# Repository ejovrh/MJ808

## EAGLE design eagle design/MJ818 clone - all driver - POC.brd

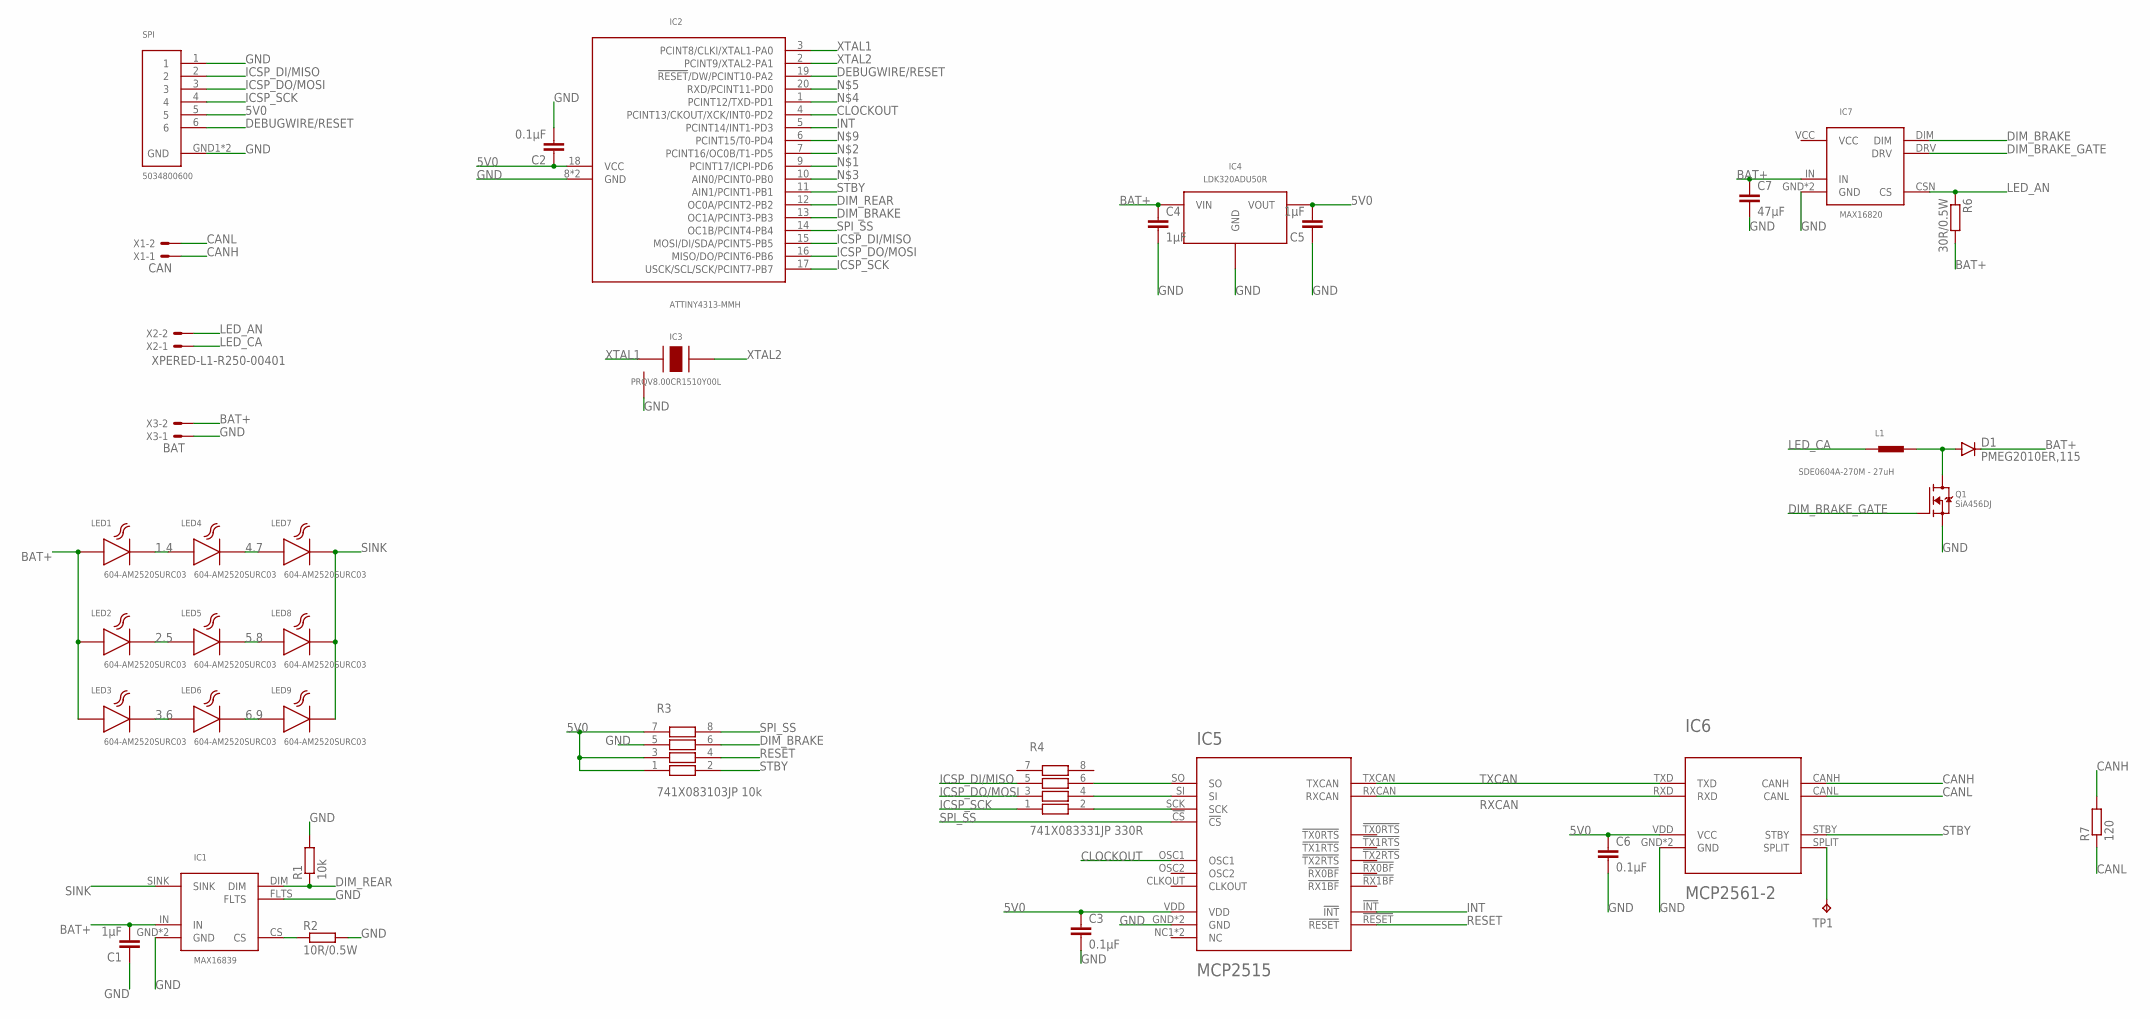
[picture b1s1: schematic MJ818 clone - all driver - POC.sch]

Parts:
C1, C4, C5: 1μF; C0402
C2, C3, C6: 0.1μF; C0402
C7: 47μF; C0805
D1: PMEG2010ER,115; SOD123
IC1: MAX16839; TDFN-6-EP
IC2: ATTINY4313-MMH; VQFN-20
IC3: PRQV8.00CR1510Y00L; SMT
IC4: LDK320ADU50R; SOT-89-D
IC5: MCP2515; QFN20
IC6: MCP2561-2; DFN10
IC7: MAX16820; TDFN-6-EP
L1: SDE0604A-270M - 27uH; SMT
LED1, LED2, LED3, LED4, LED5, LED6, LED7, LED8, LED9: 604-AM2520SURC03; SMD
Q1: SiA456DJ; SC-70-6
R1: 10k; R0402
R2: 10R/0.5W; R0603
R3: 741X083103JP 10k; 0402
R4: 741X083331JP 330R; 0402
R6: 30R/0.5W; R1206
R7: 120; R0805
SPI: 5034800600; SMT
TP1: TPB2,54; B2,54
X1: CAN; 22-23-2021
X2: XPERED-L1-R250-00401; 22-23-2021
X3: BAT; 22-23-2021

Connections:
1.4: LED1.C, LED4.A
2.5: LED2.C, LED5.A
3.6: LED3.C, LED6.A
4.7: LED4.C, LED7.A
5.8: LED5.C, LED8.A
5V0: C2.1, C3.1, C5.2, C6.1, IC2.18 (VCC), IC4.VOUT, IC5.VDD, IC6.VDD (VCC), R3.1, R3.3, R3.7, SPI.5
6.9: LED6.C, LED9.A
BAT+: C1.2, C4.1, C7.1, D1.C, IC1.IN, IC4.VIN, IC7.IN, LED1.A, LED2.A, LED3.A, R6.2, X3.2
CANH: IC6.CANH, R7.2, X1.1
CANL: IC6.CANL, R7.1, X1.2
CLOCKOUT: IC2.4 (PCINT13/CKOUT/XCK/INT0-PD2), IC5.OSC1
CS: IC1.CS, R2.1
DEBUGWIRE/RESET: IC2.19 (!RESET!/DW/PCINT10-PA2), SPI.6
DIM_BRAKE: IC2.13 (OC1A/PCINT3-PB3), IC7.DIM, R3.6
DIM_BRAKE_DRAIN: D1.A, L1.P$2, Q1.D
DIM_BRAKE_GATE: IC7.DRV, Q1.G
DIM_REAR: IC1.DIM, IC2.12 (OC0A/PCINT2-PB2), R1.1
GND: C1.1, C2.2, C3.2, C4.2, C5.1, C6.2, C7.2, IC1.FLTS, IC1.GND, IC1.GND1 (GND), IC2.8 (GND), IC2.GND, IC3.GND, IC4.GND, IC5.GND, IC5.GND6 (GND), IC6.GND, IC6.VSS (GND), IC7.GND, IC7.GND1 (GND), Q1.S, R1.2, R2.2, R3.5, SPI.1, SPI.GND1 (GND), SPI.GND2 (GND), X3.1
ICSP_DI/MISO: IC2.15 (MOSI/DI/SDA/PCINT5-PB5), R4.5, SPI.2
ICSP_DO/MOSI: IC2.16 (MISO/DO/PCINT6-PB6), R4.3, SPI.3
ICSP_SCK: IC2.17 (USCK/SCL/SCK/PCINT7-PB7), R4.1, SPI.4
INT: IC2.5 (PCINT14/INT1-PD3), IC5.!INT!
LED_AN: IC7.CSN (CS), R6.1, X2.2
LED_CA: L1.P$1, X2.1
RESET: IC5.!RESET!, R3.4
RXCAN: IC5.RXCAN, IC6.RXD
SINK: IC1.SINK, LED7.C, LED8.C, LED9.C
SPI_MISO: IC5.SO, R4.6
SPI_MOSI: IC5.SI, R4.4
SPI_SCK: IC5.SCK, R4.2
SPI_SS: IC2.14 (OC1B/PCINT4-PB4), IC5.!CS!, R3.8
SPLIT: IC6.SPLIT, TP1.TP
STBY: IC2.11 (AIN1/PCINT1-PB1), IC6.STBY, R3.2
TXCAN: IC5.TXCAN, IC6.TXD
VCC: IC7.VCC
XTAL1: IC2.3 (PCINT8/CLKI/XTAL1-PA0), IC3.XTAL1
XTAL2: IC2.2 (PCINT9/XTAL2-PA1), IC3.XTAL2

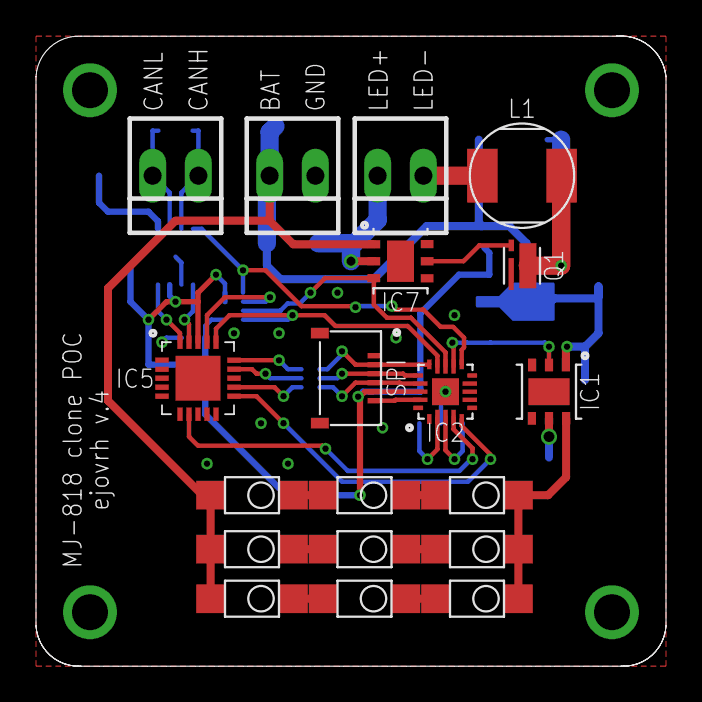
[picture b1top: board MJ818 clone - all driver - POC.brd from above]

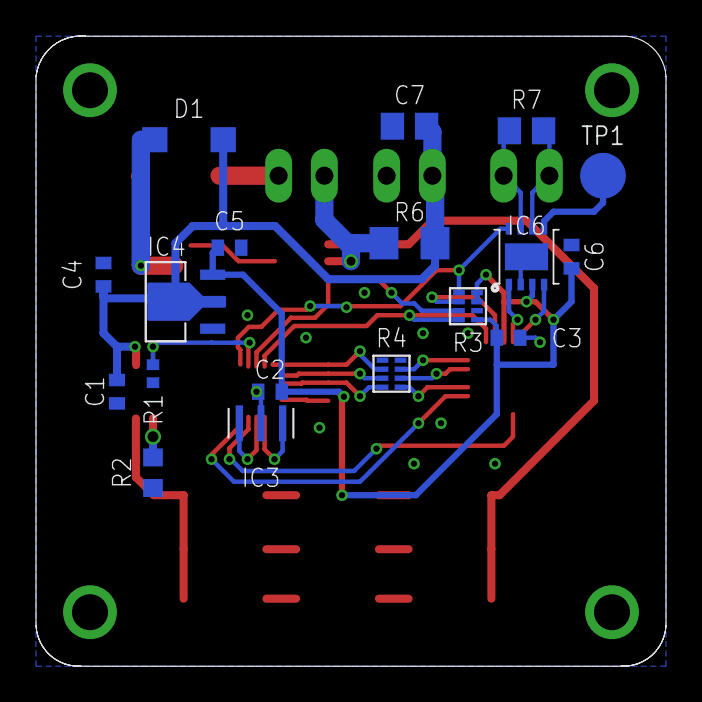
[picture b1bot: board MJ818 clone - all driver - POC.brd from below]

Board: 2 copper layers, 35.0 x 35.0 mm, 37 parts (18 on the bottom side), 36 nets.

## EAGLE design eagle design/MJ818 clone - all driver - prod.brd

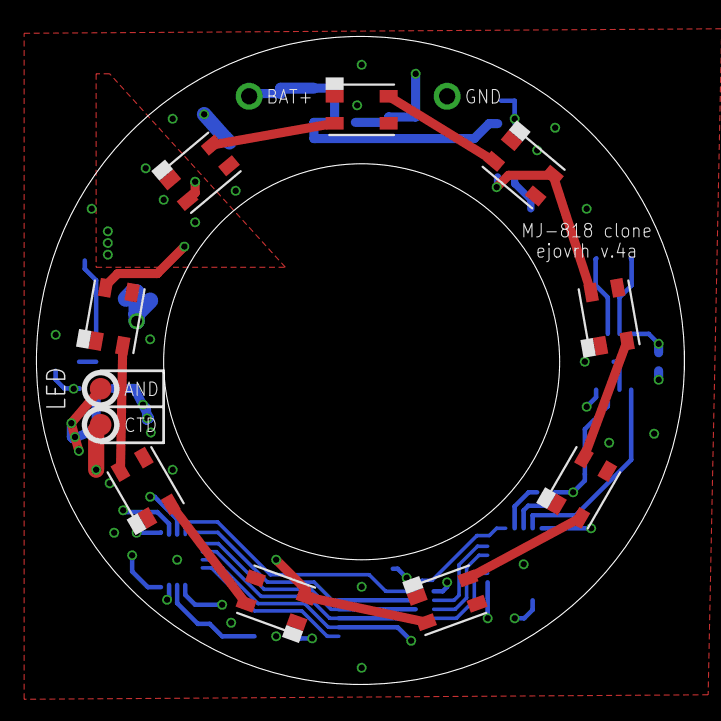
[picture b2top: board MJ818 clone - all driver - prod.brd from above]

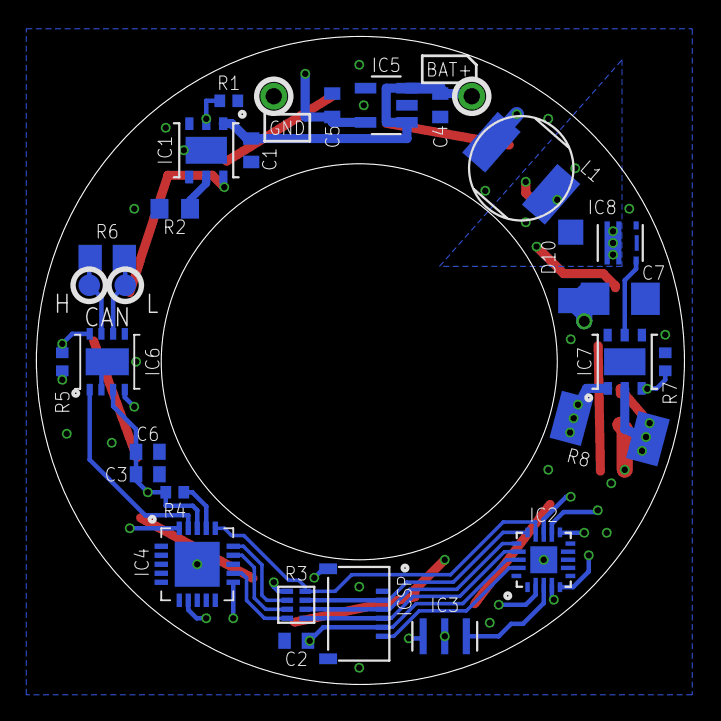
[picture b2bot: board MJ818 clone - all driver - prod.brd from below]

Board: 4 copper layers, 36.0 x 36.0 mm, 41 parts (30 on the bottom side), 35 nets.

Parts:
AND: LED anode; SMT-1.2MM
BAT+: bat+; TH-0.9MM
C1, C4, C5: 1μF; C0402
C2, C3, C6: 0.1μF; C0402
C7: 47μF; C1206
CTD: LED cathode; SMT-1.2MM
D1, D2, D3, D4, D5, D6, D7, D8, D9: CLM2D-RCC-CZ0B0BB3; SMD
D10: PMEG2010ER,115; SOD123
GND: gnd; TH-0.9MM
H: LED anode; SMT-1.2MM
IC1: MAX16839; TDFN-6-EP
IC2: ATTINY4313-MMH; VQFN-20
IC3: PBRC8.00GR50X000; SMT
IC4: MCP2515; QFN20
IC5: LDK320M50R; SOT-23-5L
IC6: MCP2561-2; DFN10
IC7: MAX16820; TDFN-6-EP
IC8: SQA470EEJ-T1_GE3; SC-70-6
ICSP: 5034800600; SMT
L: LED anode; SMT-1.2MM
L1: SDE0604A-270M - 27uH; SMT
R1, R4, R5, R7: 10k; R0402
R2: 10R/0.5W; R0603
R3: 741X083331JP 330R; 0402
R6: 120; R0805
R8: WSLT2010R2200FEB18 / 0.22Ohm 1W; R2010

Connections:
1.4: D1.4, D4.2
2.5: D2.4, D5.2
3.6: D3.4, D6.2
4.7: D4.4, D7.2
5.8: D5.4, D8.2
5V0: C2.1, C3.1, C5.2, C6.1, IC2.18, IC4.VDD, IC5.OUT, IC6.VDD, ICSP.5, R3.2, R4.1, R5.1
6.9: D6.4, D9.2
BAT+: BAT+.TP$1, C1.2, C4.1, C7.1, D1.2, D2.2, D3.2, D10.C, IC1.IN, IC5.EN, IC5.IN, IC7.IN, R8.2
CANH: H.P$1, IC6.CANH, R6.2
CANL: IC6.CANL, L.P$1, R6.1
CLOCKOUT: IC2.4, IC4.OSC1
CS: IC1.CS, R2.1
DEBUGWIRE/RESET: IC2.19, ICSP.6
DIM_BRAKE: IC2.13, IC7.DIM, R7.1
DIM_BRAKE_DRAIN: D10.A, IC8.1D, IC8.2D, IC8.5D, IC8.6D, IC8.D, L1.P$2
DIM_BRAKE_GATE: IC7.DRV, IC8.3G
DIM_REAR: IC1.DIM, IC2.12, R1.1
GND: C1.1, C2.2, C3.2, C4.2, C5.1, C6.2, C7.2, GND.TP$1, IC1.FLTS, IC1.GND, IC1.GND1, IC2.8, IC2.GND, IC3.GND, IC4.GND, IC4.GND6, IC5.GND, IC6.GND, IC6.VSS, IC7.GND, IC7.GND1, IC8.4S, IC8.S, ICSP.1, ICSP.GND1, ICSP.GND2, R1.2, R2.2, R7.2
ICSP_DI/MISO: IC2.15, ICSP.2, R3.3
ICSP_DO/MOSI: IC2.16, ICSP.3, R3.5
ICSP_SCK: IC2.17, ICSP.4, R3.7
INT: IC2.5, IC4.!INT!
LED_AN: AND.P$1, IC7.CSN, R8.1
LED_CA: CTD.P$1, L1.P$1
RESET: IC4.!RESET!, R4.2
RXCAN: IC4.RXCAN, IC6.RXD
SINK: D7.4, D8.4, D9.4, IC1.SINK
SPI_MISO: IC4.SO, R3.4
SPI_MOSI: IC4.SI, R3.6
SPI_SCK: IC4.SCK, R3.8
SPI_SS: IC2.14, IC4.!CS!, R3.1
STBY: IC2.11, IC6.STBY, R5.2
TXCAN: IC4.TXCAN, IC6.TXD
XTAL1: IC2.3, IC3.XTAL1
XTAL2: IC2.2, IC3.XTAL2

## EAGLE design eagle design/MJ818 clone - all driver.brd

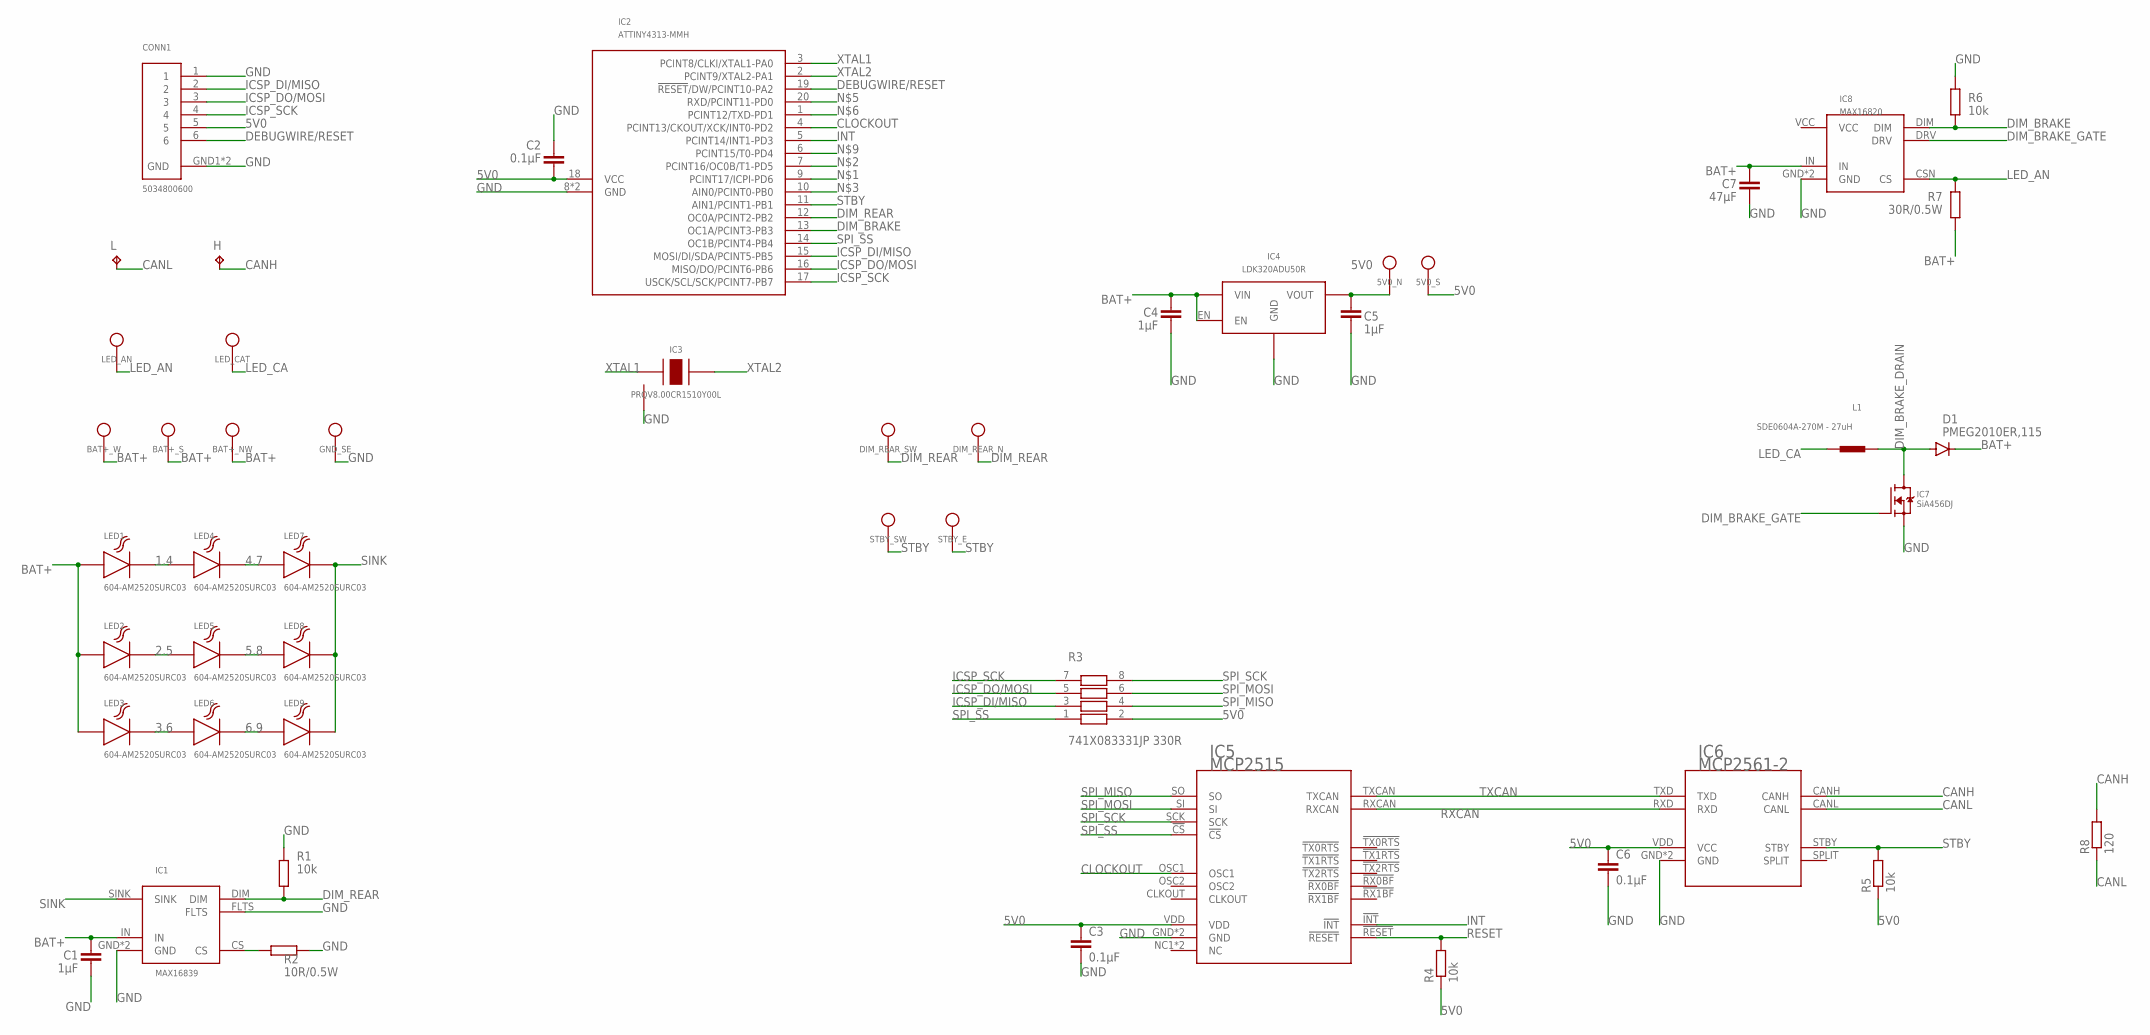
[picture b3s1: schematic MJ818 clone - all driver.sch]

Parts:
5V0_N, 5V0_S: TPTH; TH
BAT+_NW: TPTH; TH
BAT+_S: TPSMT; SMT
BAT+_W: TPTH; TH
C1, C4, C5: 1μF; C0402
C2: 0.1μF; C0402
C3, C6: 0.1μF; C1206
C7: 47μF; C1206
CONN1: 5034800600; SMT
D1: PMEG2010ER,115; SOD123
DIM_REAR_N: TPTH; TH
DIM_REAR_SW: TPTH; TH
GND_SE: TPTH; TH
H: TPB2,54; B2,54
IC1: MAX16839; TDFN-6-EP
IC2: ATTINY4313-MMH; VQFN-20
IC3: PRQV8.00CR1510Y00L; SMT
IC4: LDK320ADU50R; SOT-23-5L
IC5: MCP2515; QFN20
IC6: MCP2561-2; DFN10
IC7: SiA456DJ; SC-70-6
IC8: MAX16820; TDFN-6-EP
L: TPB2,54; B2,54
L1: SDE0604A-270M - 27uH; SMT
LED1, LED2, LED3, LED4, LED5, LED6, LED7, LED8, LED9: 604-AM2520SURC03; SMD
LED_AN: TPTH; TH
LED_CAT: TPTH; TH
R1, R4, R6: 10k; R0402
R2: 10R/0.5W; R0603
R3: 741X083331JP 330R; 0402
R5: 10k; R0603
R7: 30R/0.5W; R1206
R8: 120; R0805
STBY_E: TPTH; TH
STBY_SW: TPTH; TH

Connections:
1.4: LED1.C, LED4.A
2.5: LED2.C, LED5.A
3.6: LED3.C, LED6.A
4.7: LED4.C, LED7.A
5.8: LED5.C, LED8.A
5V0: 5V0_N.TP$1, 5V0_S.TP$1, C2.1, C3.1, C5.2, C6.1, CONN1.5, IC2.18 (VCC), IC4.OUT (VOUT), IC5.VDD, IC6.VDD (VCC), R3.2, R4.1, R5.1
6.9: LED6.C, LED9.A
BAT+: BAT+_NW.TP$1, BAT+_S.P$1, BAT+_W.TP$1, C1.2, C4.1, C7.1, D1.C, IC1.IN, IC4.EN, IC4.IN (VIN), IC8.IN, LED1.A, LED2.A, LED3.A, R7.2
CANH: H.TP, IC6.CANH, R8.2
CANL: IC6.CANL, L.TP, R8.1
CLOCKOUT: IC2.4 (PCINT13/CKOUT/XCK/INT0-PD2), IC5.OSC1
CS: IC1.CS, R2.1
DEBUGWIRE/RESET: CONN1.6, IC2.19 (!RESET!/DW/PCINT10-PA2)
DIM_BRAKE: IC2.13 (OC1A/PCINT3-PB3), IC8.DIM, R6.1
DIM_BRAKE_DRAIN: D1.A, IC7.D, L1.P$2
DIM_BRAKE_GATE: IC7.G, IC8.DRV
DIM_REAR: DIM_REAR_N.TP$1, DIM_REAR_SW.TP$1, IC1.DIM, IC2.12 (OC0A/PCINT2-PB2), R1.1
GND: C1.1, C2.2, C3.2, C4.2, C5.1, C6.2, C7.2, CONN1.1, CONN1.GND1 (GND), CONN1.GND2 (GND), GND_SE.TP$1, IC1.FLTS, IC1.GND, IC1.GND1 (GND), IC2.8 (GND), IC2.GND, IC3.GND, IC4.GND, IC5.GND, IC5.GND6 (GND), IC6.GND, IC6.VSS (GND), IC7.S, IC8.GND, IC8.GND1 (GND), R1.2, R2.2, R6.2
ICSP_DI/MISO: CONN1.2, IC2.15 (MOSI/DI/SDA/PCINT5-PB5), R3.3
ICSP_DO/MOSI: CONN1.3, IC2.16 (MISO/DO/PCINT6-PB6), R3.5
ICSP_SCK: CONN1.4, IC2.17 (USCK/SCL/SCK/PCINT7-PB7), R3.7
INT: IC2.5 (PCINT14/INT1-PD3), IC5.!INT!
LED_AN: IC8.CSN (CS), LED_AN.TP$1, R7.1
LED_CA: L1.P$1, LED_CAT.TP$1
RESET: IC5.!RESET!, R4.2
RXCAN: IC5.RXCAN, IC6.RXD
SINK: IC1.SINK, LED7.C, LED8.C, LED9.C
SPI_MISO: IC5.SO, R3.4
SPI_MOSI: IC5.SI, R3.6
SPI_SCK: IC5.SCK, R3.8
SPI_SS: IC2.14 (OC1B/PCINT4-PB4), IC5.!CS!, R3.1
STBY: IC2.11 (AIN1/PCINT1-PB1), IC6.STBY, R5.2, STBY_E.TP$1, STBY_SW.TP$1
TXCAN: IC5.TXCAN, IC6.TXD
VCC: IC8.VCC
XTAL1: IC2.3 (PCINT8/CLKI/XTAL1-PA0), IC3.XTAL1
XTAL2: IC2.2 (PCINT9/XTAL2-PA1), IC3.XTAL2

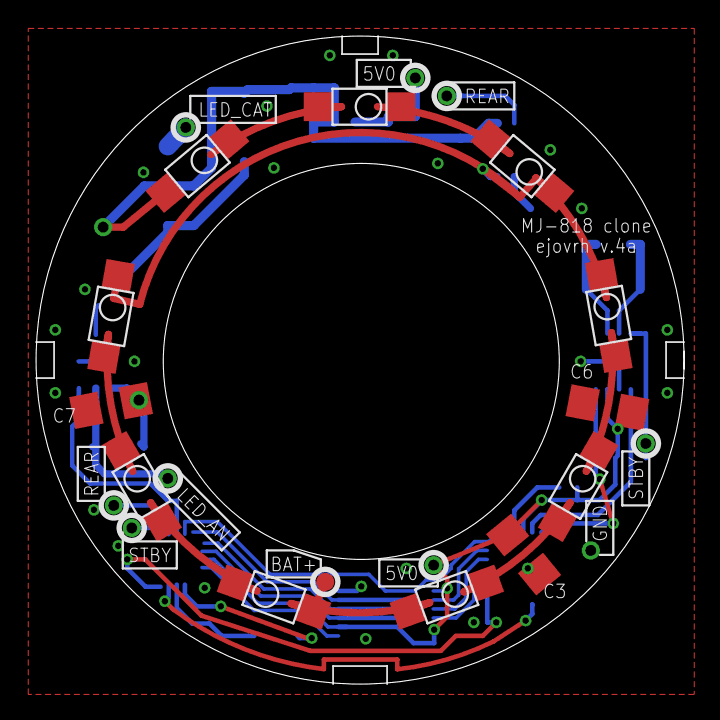
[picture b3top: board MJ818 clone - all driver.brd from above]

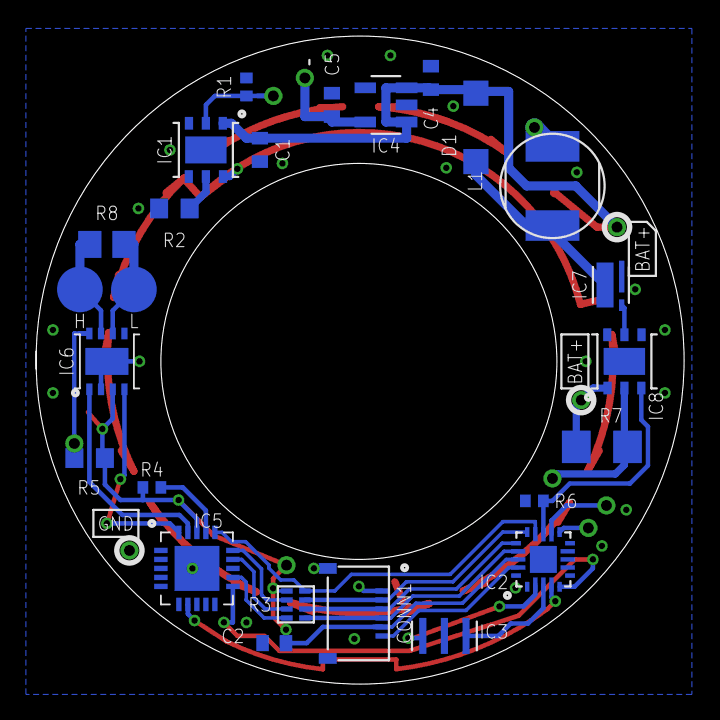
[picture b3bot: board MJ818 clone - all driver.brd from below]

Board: 2 copper layers, 36.0 x 36.0 mm, 49 parts (28 on the bottom side), 35 nets.

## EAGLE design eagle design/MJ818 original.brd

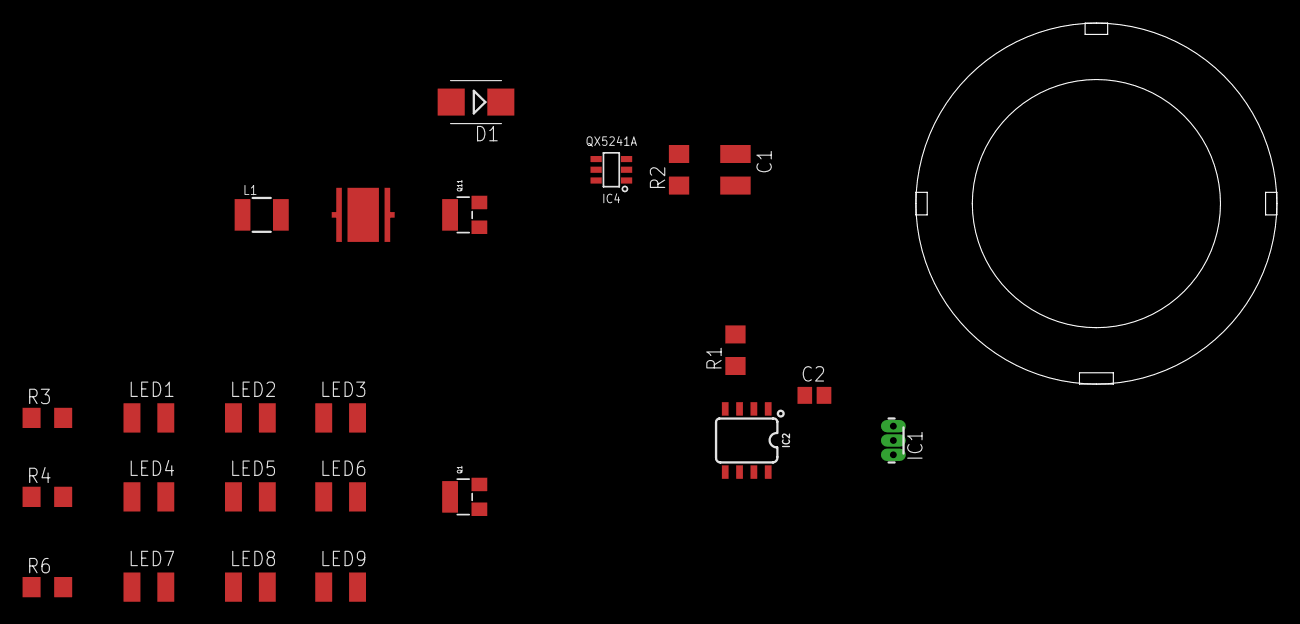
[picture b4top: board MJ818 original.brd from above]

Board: 2 copper layers, 32.0 x 32.0 mm, 24 parts (0 on the bottom side), 20 nets, no tracks yet.

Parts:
C1: 11uF; C3225
C2: 1uF; C2012
D1: MBRS130LT3; SMB
IC1: 48104 AVR21; SIP3-UA
IC2: ATTINY13SOIC; SO08_MCU
IC4: QX5241A; SOT-23-6
L1: 470uH; MS50
LED1, LED2, LED3, LED4, LED5, LED6, LED7, LED8, LED9: GM5BW96385A
LED10: CREE-XLAMP-XM-L
Q1, Q11: SOT23-W
R1: inf; R3216
R2: 0.25; R3216
R3, R4, R6: 100; R3216

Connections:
CSN: IC4.CSN, L1.1, R2.1
DIM: IC2.5, IC4.DIM
GND: C1.2, C2.2, IC1.2, IC2.8, IC4.GND, Q1.2, Q11.2, R1.2
LED: L1.2, LED10.A, LED10.A@1
MAGNET_SENSE: IC1.3, IC2.2
unnamed: LED1.C, LED2.A
unnamed: LED2.C, LED3.A
unnamed: LED7.C, LED8.A
unnamed: LED8.C, LED9.A
unnamed: LED1.A, R3.2
unnamed: LED4.A, R4.2
unnamed: LED4.C, LED5.A
unnamed: LED5.C, LED6.A
unnamed: LED7.A, R6.2
unnamed: IC2.3, R1.1
Q1_GATE: IC4.DRV, Q11.1
Q2_DRAIN: D1.A, LED3.C, LED6.C, LED9.C, LED10.C, LED10.C@1, Q1.3, Q11.3
Q2_GATE: IC2.7, Q1.1
SUPPLY_INNER: C1.1, D1.C, IC4.VIN, R2.2, R3.1, R4.1, R6.1
VCC: C2.1, IC1.1, IC2.1, IC4.VCC

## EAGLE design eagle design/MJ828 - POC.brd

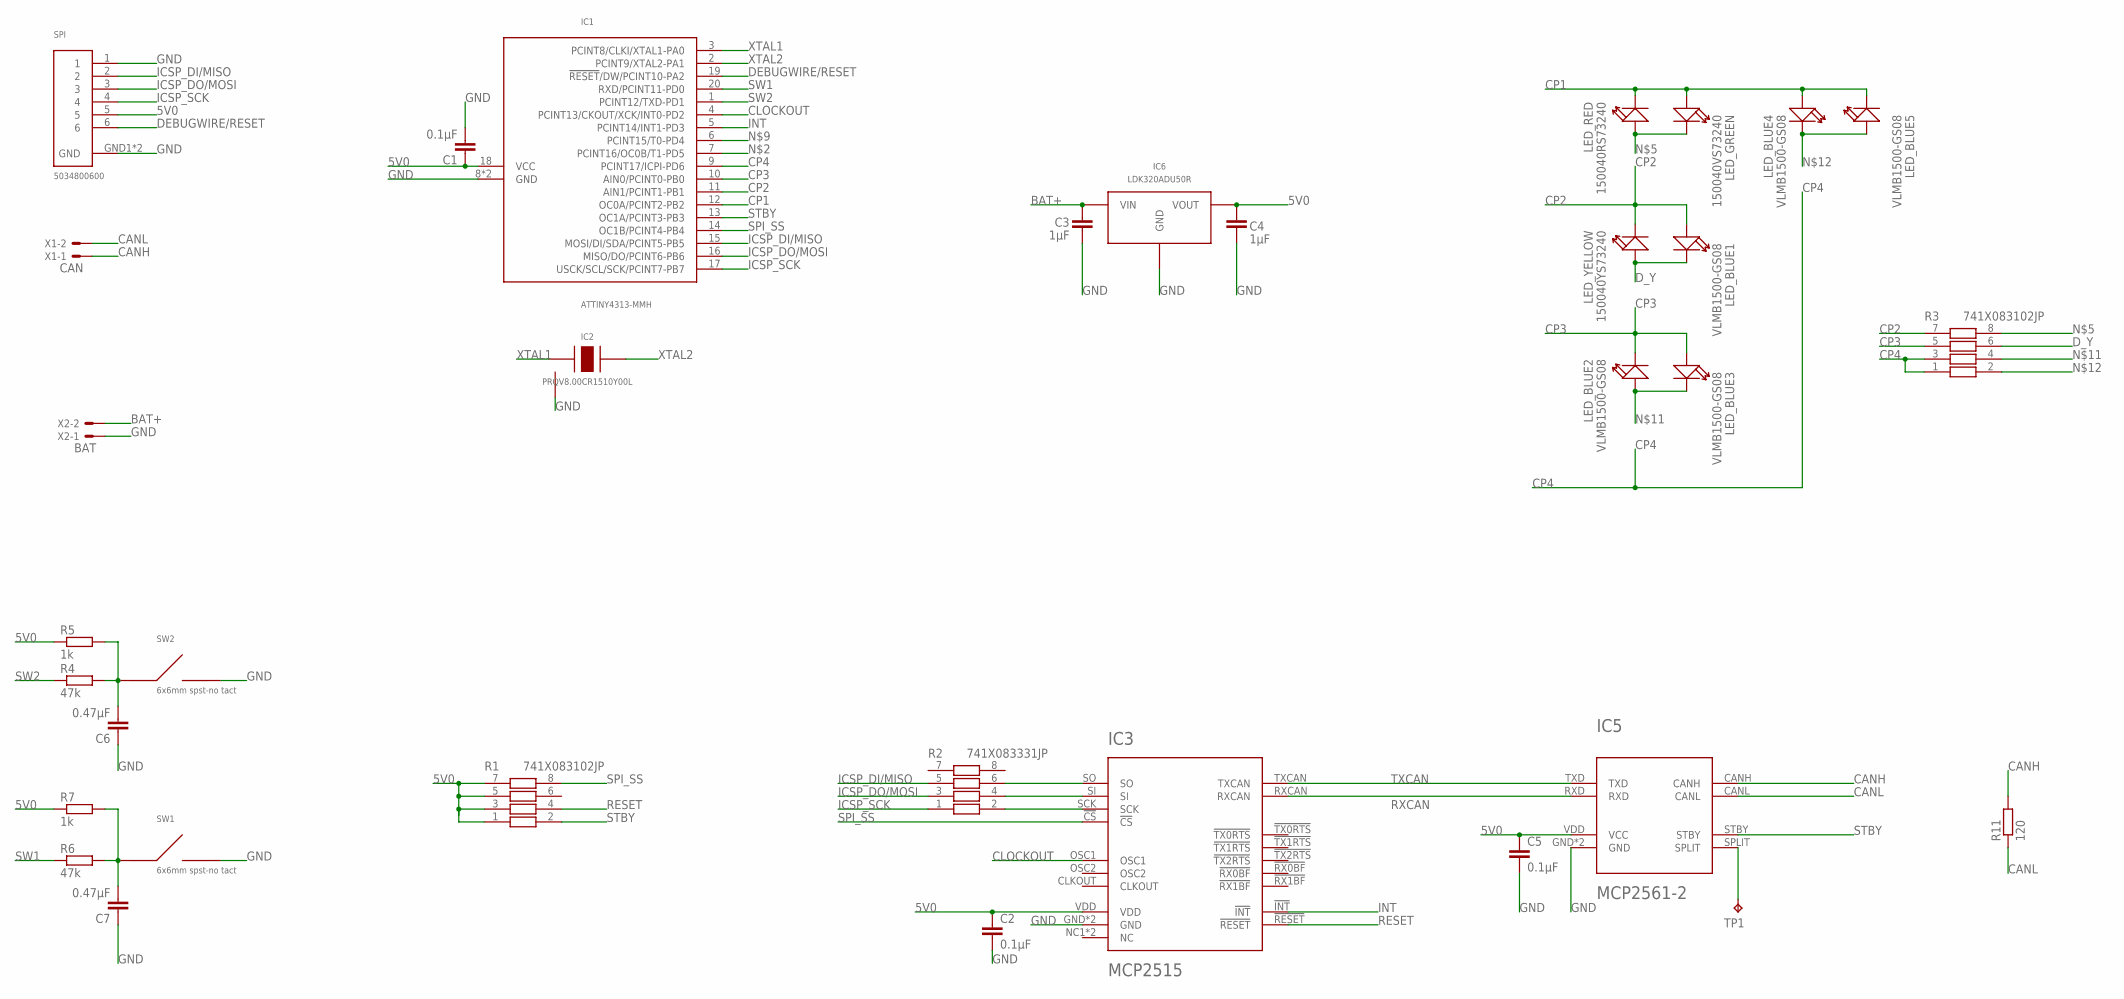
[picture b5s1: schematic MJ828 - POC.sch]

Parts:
C1, C2, C5: 0.1μF; C0402
C3, C4: 1μF; C0402
C6, C7: 0.47μF; C0402
IC1: ATTINY4313-MMH; VQFN-20
IC2: PRQV8.00CR1510Y00L; SMT
IC3: MCP2515; QFN20
IC5: MCP2561-2; DFN10
IC6: LDK320ADU50R; SOT-89
LED_BLUE1, LED_BLUE2, LED_BLUE3, LED_BLUE4, LED_BLUE5: VLMB1500-GS08; LED-0402
LED_GREEN: 150040VS73240; LED-0402
LED_RED: 150040RS73240; LED-0402
LED_YELLOW: 150040YS73240; LED-0402
R1, R3: 741X083102JP; 0402
R2: 741X083331JP; 0402
R4, R6: 47k; R0402
R5, R7: 1k; R0402
R11: 120; R0805
SPI: 5034800600; SMT
SW1, SW2: 6x6mm spst-no tact; SMD
TP1: TPB2,54; B2,54
X1: CAN; 22-23-2021
X2: BAT; 22-23-2021

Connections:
5V0: C1.1, C2.1, C4.2, C5.1, IC1.18 (VCC), IC3.VDD, IC5.VDD (VCC), IC6.VOUT, R1.1, R1.3, R1.5, R1.7, R5.1, R7.1, SPI.5
BAT+: C3.1, IC6.VIN, X2.2
CANH: IC5.CANH, R11.2, X1.1
CANL: IC5.CANL, R11.1, X1.2
CLOCKOUT: IC1.4 (PCINT13/CKOUT/XCK/INT0-PD2), IC3.OSC1
CP1: IC1.12 (OC0A/PCINT2-PB2), LED_BLUE4.+, LED_BLUE5.-, LED_GREEN.+, LED_RED.-
CP2: IC1.11 (AIN1/PCINT1-PB1), LED_BLUE1.+, LED_YELLOW.-, R3.7
CP3: IC1.10 (AIN0/PCINT0-PB0), LED_BLUE2.-, LED_BLUE3.+, R3.5
CP4: IC1.9 (PCINT17/ICPI-PD6), R3.1, R3.3
DEBUGWIRE/RESET: IC1.19 (!RESET!/DW/PCINT10-PA2), SPI.6
D_Y: LED_BLUE1.-, LED_YELLOW.+, R3.6
GND: C1.2, C2.2, C3.2, C4.1, C5.2, C6.1, C7.1, IC1.8 (GND), IC1.GND, IC2.GND, IC3.GND, IC3.GND6 (GND), IC5.GND, IC5.VSS (GND), IC6.GND, SPI.1, SPI.GND1 (GND), SPI.GND2 (GND), SW1.3, SW1.4, SW2.3, SW2.4, X2.1
ICSP_DI/MISO: IC1.15 (MOSI/DI/SDA/PCINT5-PB5), R2.5, SPI.2
ICSP_DO/MOSI: IC1.16 (MISO/DO/PCINT6-PB6), R2.3, SPI.3
ICSP_SCK: IC1.17 (USCK/SCL/SCK/PCINT7-PB7), R2.1, SPI.4
INT: IC1.5 (PCINT14/INT1-PD3), IC3.!INT!
unnamed: C6.2, R4.2, R5.2, SW2.1, SW2.2
unnamed: LED_GREEN.-, LED_RED.+, R3.8
unnamed: C7.2, R6.2, R7.2, SW1.1, SW1.2
unnamed: LED_BLUE2.+, LED_BLUE3.-, R3.4
unnamed: LED_BLUE4.-, LED_BLUE5.+, R3.2
RESET: IC3.!RESET!, R1.4
RXCAN: IC3.RXCAN, IC5.RXD
SPI_SCK: IC3.SCK, R2.2
SPI_SI: IC3.SI, R2.4
SPI_SO: IC3.SO, R2.6
SPI_SS: IC1.14 (OC1B/PCINT4-PB4), IC3.!CS!, R1.8
SPLIT: IC5.SPLIT, TP1.TP
STBY: IC1.13 (OC1A/PCINT3-PB3), IC5.STBY, R1.2
SW1: IC1.20 (RXD/PCINT11-PD0), R6.1
SW2: IC1.1 (PCINT12/TXD-PD1), R4.1
TXCAN: IC3.TXCAN, IC5.TXD
XTAL1: IC1.3 (PCINT8/CLKI/XTAL1-PA0), IC2.XTAL1
XTAL2: IC1.2 (PCINT9/XTAL2-PA1), IC2.XTAL2

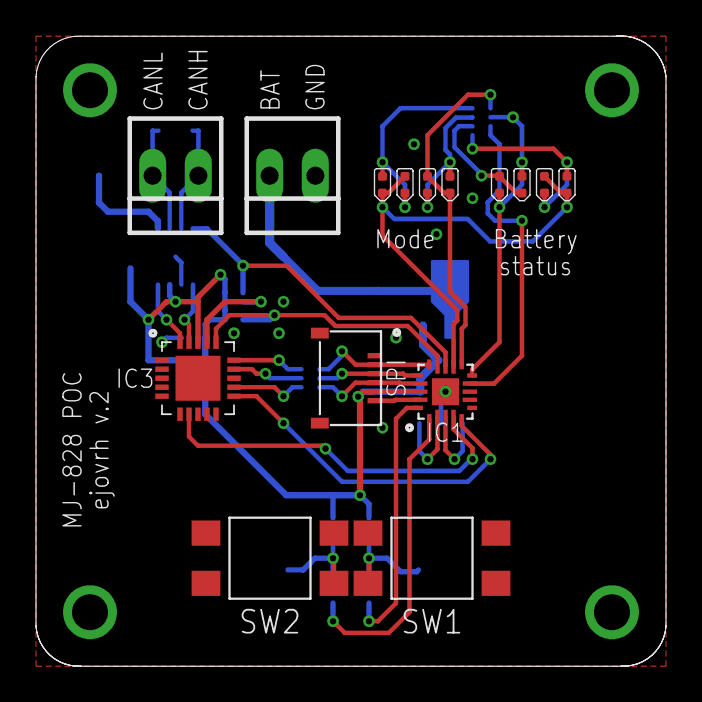
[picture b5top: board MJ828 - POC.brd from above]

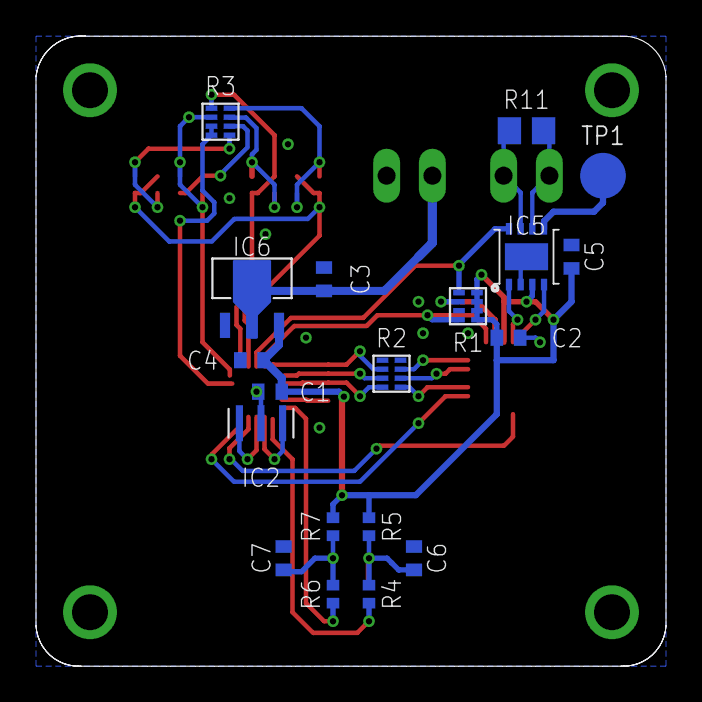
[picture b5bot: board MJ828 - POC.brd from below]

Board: 2 copper layers, 35.0 x 35.0 mm, 34 parts (19 on the bottom side), 34 nets.

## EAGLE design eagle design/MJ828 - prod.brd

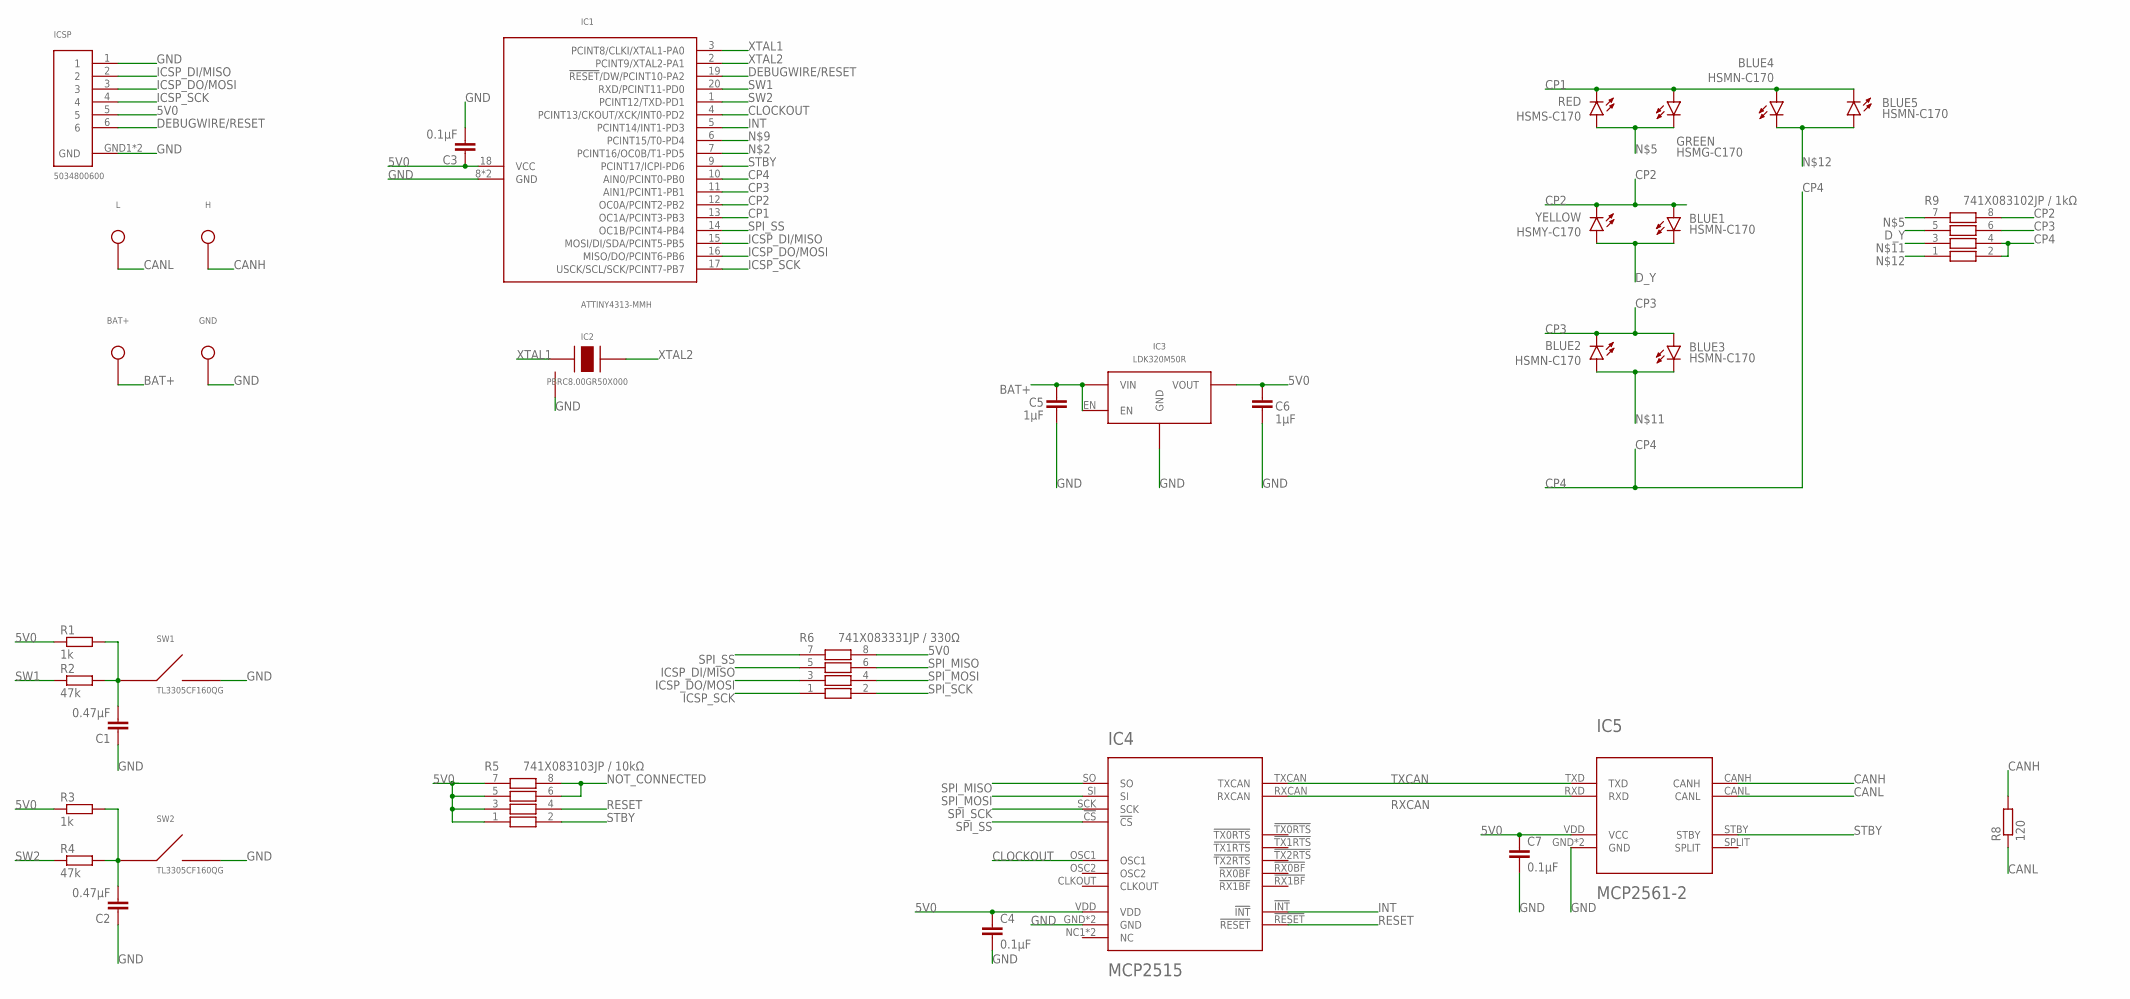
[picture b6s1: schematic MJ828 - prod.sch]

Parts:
BAT+: 8V4 Battery +; TH-0.9MM
BLUE1, BLUE2, BLUE3, BLUE4, BLUE5: HSMN-C170; SML0805
C1, C2: 0.47μF; C0402
C3, C4, C7: 0.1μF; C0402
C5, C6: 1μF; C0402
GND: Ground; TH-0.9MM
GREEN: HSMG-C170; SML0805
H: CAN High; TH-0.9MM
IC1: ATTINY4313-MMH; VQFN-20
IC2: PBRC8.00GR50X000; SMT
IC3: LDK320M50R; SOT-23-5L
IC4: MCP2515; QFN20
IC5: MCP2561-2; DFN10
ICSP: 5034800600; SMT
L: CAN Low; TH-0.9MM
R1, R3: 1k; R0402
R2, R4: 47k; R0402
R5: 741X083103JP / 10kΩ; 0402
R6: 741X083331JP / 330Ω; 0402
R8: 120; R0402
R9: 741X083102JP / 1kΩ; 0402
RED: HSMS-C170; SML0805
SW1, SW2: TL3305CF160QG; SMD
YELLOW: HSMY-C170; SML0805

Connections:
5V0: C3.1, C4.1, C6.2, C7.1, IC1.18 (VCC), IC3.OUT (VOUT), IC4.VDD, IC5.VDD (VCC), ICSP.5, R1.1, R3.1, R5.1, R5.3, R5.5, R5.7, R6.8
BAT+: BAT+.TP$1, C5.1, IC3.EN, IC3.IN (VIN)
CANH: H.TP$1, IC5.CANH, R8.2
CANL: IC5.CANL, L.TP$1, R8.1
CLOCKOUT: IC1.4 (PCINT13/CKOUT/XCK/INT0-PD2), IC4.OSC1
CP1: BLUE4.A, BLUE5.C, GREEN.A, IC1.13 (OC1A/PCINT3-PB3), RED.C
CP2: BLUE1.A, IC1.12 (OC0A/PCINT2-PB2), R9.8, YELLOW.C
CP3: BLUE2.C, BLUE3.A, IC1.11 (AIN1/PCINT1-PB1), R9.6
CP4: IC1.10 (AIN0/PCINT0-PB0), R9.2, R9.4
DEBUGWIRE/RESET: IC1.19 (!RESET!/DW/PCINT10-PA2), ICSP.6
D_Y: BLUE1.C, R9.5, YELLOW.A
GND: C1.1, C2.1, C3.2, C4.2, C5.2, C6.1, C7.2, GND.TP$1, IC1.8 (GND), IC1.GND, IC2.GND, IC3.GND, IC4.GND, IC4.GND6 (GND), IC5.GND, IC5.VSS (GND), ICSP.1, ICSP.GND1 (GND), ICSP.GND2 (GND), SW1.3, SW1.4, SW2.3, SW2.4
ICSP_DI/MISO: IC1.15 (MOSI/DI/SDA/PCINT5-PB5), ICSP.2, R6.5
ICSP_DO/MOSI: IC1.16 (MISO/DO/PCINT6-PB6), ICSP.3, R6.3
ICSP_SCK: IC1.17 (USCK/SCL/SCK/PCINT7-PB7), ICSP.4, R6.1
INT: IC1.5 (PCINT14/INT1-PD3), IC4.!INT!
unnamed: C1.2, R1.2, R2.2, SW1.1, SW1.2
unnamed: GREEN.C, R9.7, RED.A
unnamed: C2.2, R3.2, R4.2, SW2.1, SW2.2
unnamed: BLUE2.A, BLUE3.C, R9.3
unnamed: BLUE4.C, BLUE5.A, R9.1
NOT_CONNECTED: R5.6, R5.8
RESET: IC4.!RESET!, R5.4
RXCAN: IC4.RXCAN, IC5.RXD
SPI_MISO: IC4.SO, R6.6
SPI_MOSI: IC4.SI, R6.4
SPI_SCK: IC4.SCK, R6.2
SPI_SS: IC1.14 (OC1B/PCINT4-PB4), IC4.!CS!, R6.7
STBY: IC1.9 (PCINT17/ICPI-PD6), IC5.STBY, R5.2
SW1: IC1.20 (RXD/PCINT11-PD0), R2.1
SW2: IC1.1 (PCINT12/TXD-PD1), R4.1
TXCAN: IC4.TXCAN, IC5.TXD
XTAL1: IC1.3 (PCINT8/CLKI/XTAL1-PA0), IC2.XTAL1
XTAL2: IC1.2 (PCINT9/XTAL2-PA1), IC2.XTAL2

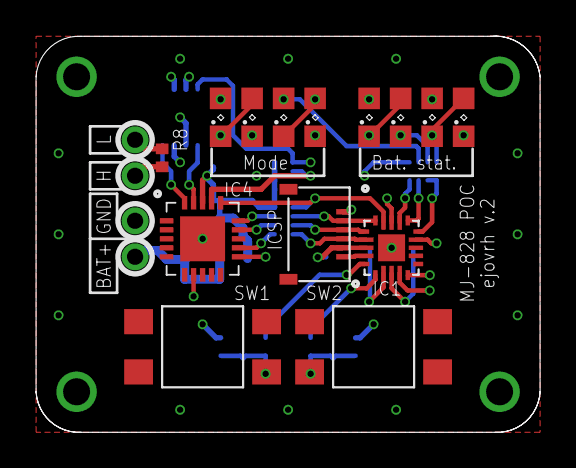
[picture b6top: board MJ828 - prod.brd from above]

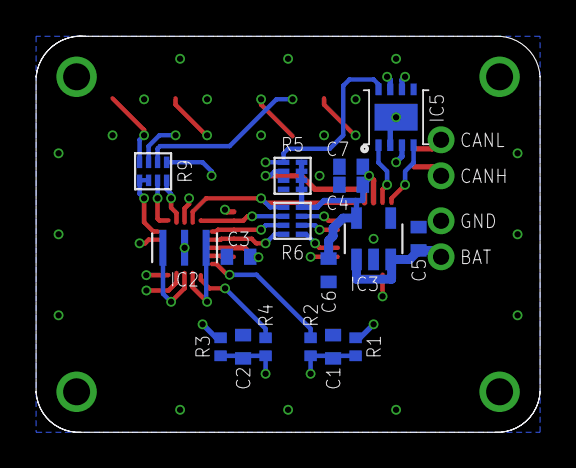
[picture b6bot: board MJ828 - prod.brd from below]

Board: 4 copper layers, 28.0 x 22.0 mm, 35 parts (17 on the bottom side), 34 nets.

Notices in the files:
parts and their libraries:
SparkFun-Retired: Licensing: Creative Commons ShareAlike 4.0 International - https://creativecommons.org/licenses/by-sa/4.0
